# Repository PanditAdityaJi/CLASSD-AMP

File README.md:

# Class-D Audio Amplifier — NE555 PWM

A low-power Class-D audio amplifier built around the NE555 timer as a PWM generator. The design covers the full signal path from microphone/line input to an 8 Ω speaker, with LTspice simulation and a KiCad PCB layout included.

---

## How It Works

```
Audio In ──► opamp ──► NE555 ──► BJT Driver ──► PMOS/NMOS ──► LC Filter ──► Speaker
            Comparator   PWM      (Q1/Q2)        Half-Bridge    33µH/470nF
```

The audio signal and a triangle carrier are compared by an op-amp running open-loop. The comparator output triggers the NE555, which produces a PWM waveform whose duty cycle tracks the audio amplitude. A complementary BJT pair buffers the PWM to fast-charge the MOSFET gates of an (PMOS) /  (NMOS) half-bridge. An LC low-pass filter strips the switching harmonics, leaving a clean audio signal for the speaker.

## NE555 Pin Connections

| Pin | Name | Connection |
|-----|------|------------|
| 1 | GND  | Ground plane |
| 2 | TRIG | Triangle carrier via 1 nF AC-coupling cap (C2) |
| 3 | OUT  | PWM → gate driver through 100 Ω series resistor (R6) |
| 4 | RST  | Tied directly to VCC — **never** to OUT |
| 5 | CV   | 10 nF cap (C3) to GND — decouples internal divider |
| 6 | THRS | Timing capacitor + R3/R4 network |
| 7 | DIS  | Between R3 (1 kΩ) and R4 (3.3 kΩ) |
| 8 | VCC  | 12 V supply |

---

## Key Design Decisions

**Why NE555 instead of a microcontroller?** Frequency is set entirely by passive components — no firmware, no clock dependency.

**Why a BJT driver stage?** Power MOSFETs have several nF of gate capacitance. Driving them straight from the 555 output produces slow edges and shoot-through overlap. The emitter follower charges and discharges the gates in tens of nanoseconds.

**Why PMOS + NMOS instead of dual N-channel with a bootstrap?** Simpler gate drive — no floating supply needed for the high side. The pair has low enough R_DS(on) (0.5–1.5 Ω) that conduction loss is small against the 8 Ω load.

**Why 100 Ω on the gate (R6)?** Without it the gate trace resonates with the MOSFET input capacitance at hundreds of MHz. 100 Ω damps the ring without slowing the edge enough to increase switching loss.

**Why 33 µH / 0.47 µF for the LC filter?** The cut-off lands at roughly 300 kHz, giving >40 dB/decade roll-off. Film caps were specified over ceramics because ceramics of this value suffer severe DC-bias derating that would shift the pole under signal swing.

**Why matched R5 = R8 = 1 kΩ in the triangle generator?** Equal resistors make the rising and falling slopes identical, producing a symmetric carrier. An asymmetric carrier introduces even-order harmonics and a DC offset at the speaker.

---

## Bill of Materials

| Ref | Part | Value | Notes |
|-----|------|-------|-------|
| U1 | NE555D | — | SOIC-8 |
| U2 | LMV321 | — | SOT-23-5, open-loop comparator |
| Q1 | 2N3904 | — | NPN gate driver |
| Q2 | 2N3906 | — | PNP gate driver |
| Q3 | IRF9540 | — | PMOS high-side switch |
| Q4 | IRF540  | — | NMOS low-side switch |
| L1 | Inductor | 33 µH | Ferrite core, ≥ 3 A rated |
| R1 | Resistor | 100 kΩ | Input bias divider |
| R2 | Resistor | 100 kΩ | Input bias divider |
| R3 | Resistor | 1 kΩ   | 555 timing (charge) |
| R4 | Resistor | 3.3 kΩ | 555 timing (discharge) |
| R5 | Resistor | 1 kΩ   | Triangle generator |
| R6 | Resistor | 100 Ω  | Gate series damping |
| R7 | Resistor | 8 Ω    | Speaker load |
| R8 | Resistor | 1 kΩ   | Triangle generator |
| C1 | Capacitor | 10 nF  | Audio input AC-coupling |
| C2 | Capacitor | 1 nF   | TRIG AC-coupling |
| C3 | Capacitor | 10 nF  | CV pin bypass |
| C4 | Capacitor | 10 nF  | Triangle timing |
| C5 | Capacitor | 0.47 µF | LC filter (film) |
| C6 | Capacitor | 0.47 µF | Output filter / DC-block (film) |
| J2 | Connector | 2-pin | Power input (24 V) |
| J3 | Connector | 2-pin | Audio input |
| J4 | Connector | 2-pin | Speaker output |
| LS1 | Speaker | 8 Ω | — |

---

## Simulation

Simulated end-to-end in LTspice with a 1 kHz / 0.5 V sine test tone.

**Verified nodes:**

- **V(triangle)** — symmetric carrier, 3.4–3.6 V swing at the carrier frequency.
- **V(gate)** — clean PWM from the 555 output stage.
- **V(switching)** — half-bridge output, full rail-to-rail (0 V ↔ 24 V).
- **V(audio_out)** — filtered output; residual ripple is only a few millivolts.

**FFT results:**

- Audio_out shows the 1 kHz tone near −55 dB with harmonics below −140 dB across the audio band.
- Switching node shows the expected carrier and odd harmonics near 100 kHz.

---

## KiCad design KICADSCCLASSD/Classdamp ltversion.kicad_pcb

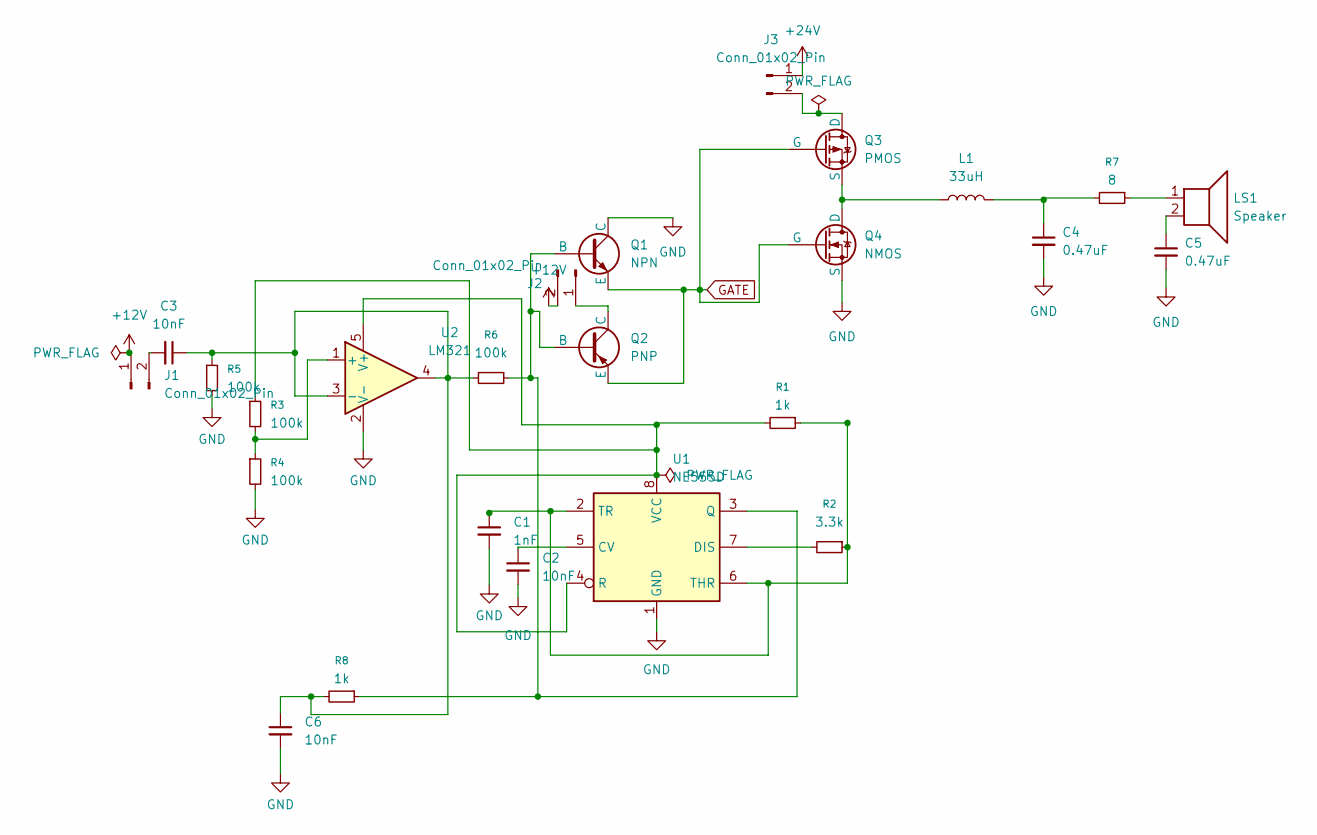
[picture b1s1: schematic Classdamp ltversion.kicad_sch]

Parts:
C1: 1nF; C_0201_0603Metric_Pad0.64x0.40mm_HandSolder
C2, C3, C6: 10nF; C_0402_1005Metric_Pad0.74x0.62mm_HandSolder
C4, C5: 0.47uF; C_0402_1005Metric_Pad0.74x0.62mm_HandSolder
J1, J2, J3: Conn_01x02_Pin; PhoenixContact_MCV_1,5_2-GF-5.08_1x02_P5.08mm_Vertical_Thre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
L1: 33uH; L_1206_3216Metric_Pad1.22x1.90mm_HandSolder
LS1: Speaker; MagneticBuzzer_ProSignal_ABT-410-RC
Q1: NPN; SOT-23
Q2: PNP; SOT-23
Q3: PMOS; TO-92
Q4: NMOS; TO-92
R1, R8: 1k; R_0201_0603Metric_Pad0.64x0.40mm_HandSolder
R2: 3.3k; R_0201_0603Metric_Pad0.64x0.40mm_HandSolder
R3, R4, R5, R6: 100k; R_0508_1220Metric_Pad1.12x2.15mm_HandSolder
R7: 8; R_0612_1632Metric_Pad1.18x3.40mm_HandSolder
U1: NE555D; SOIC-8_3.9x4.9mm_P1.27mm
U2: LM321; SOT-23-5

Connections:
+12V: J1.1, J2.2
+24V: J3.1
GATE: Q1.3 (E), Q2.3 (E), Q3.2 (G), Q4.2 (G)
GND: C1.2, C2.2, C4.2, C5.2, C6.2, Q1.1 (C), Q4.3 (S), R4.2, R5.2, U1.1 (GND), U2.2 (V-)
unnamed: C4.1, L1.2, R7.2
unnamed: C5.1, LS1.2
unnamed: C3.2, J1.2
unnamed: J2.1, Q2.1 (C)
unnamed: J3.2, Q3.1 (D)
unnamed: LS1.1, R7.1
unnamed: Q1.2 (B), Q2.2 (B), R6.1, R8.1, U1.3 (Q)
unnamed: L1.1, Q3.3 (S), Q4.1 (D)
unnamed: C2.1, U1.5 (CV)
unnamed: R2.2, U1.7 (DIS)
unnamed: R1.2, R3.1, U1.4 (R), U1.8 (VCC), U2.5 (V+)
unnamed: C1.1, R1.1, R2.1, U1.2 (TR), U1.6 (THR)
unnamed: R3.2, R4.1, U2.1 (+)
unnamed: C3.1, C6.1, R5.1, R6.2, R8.2, U2.3 (-), U2.4

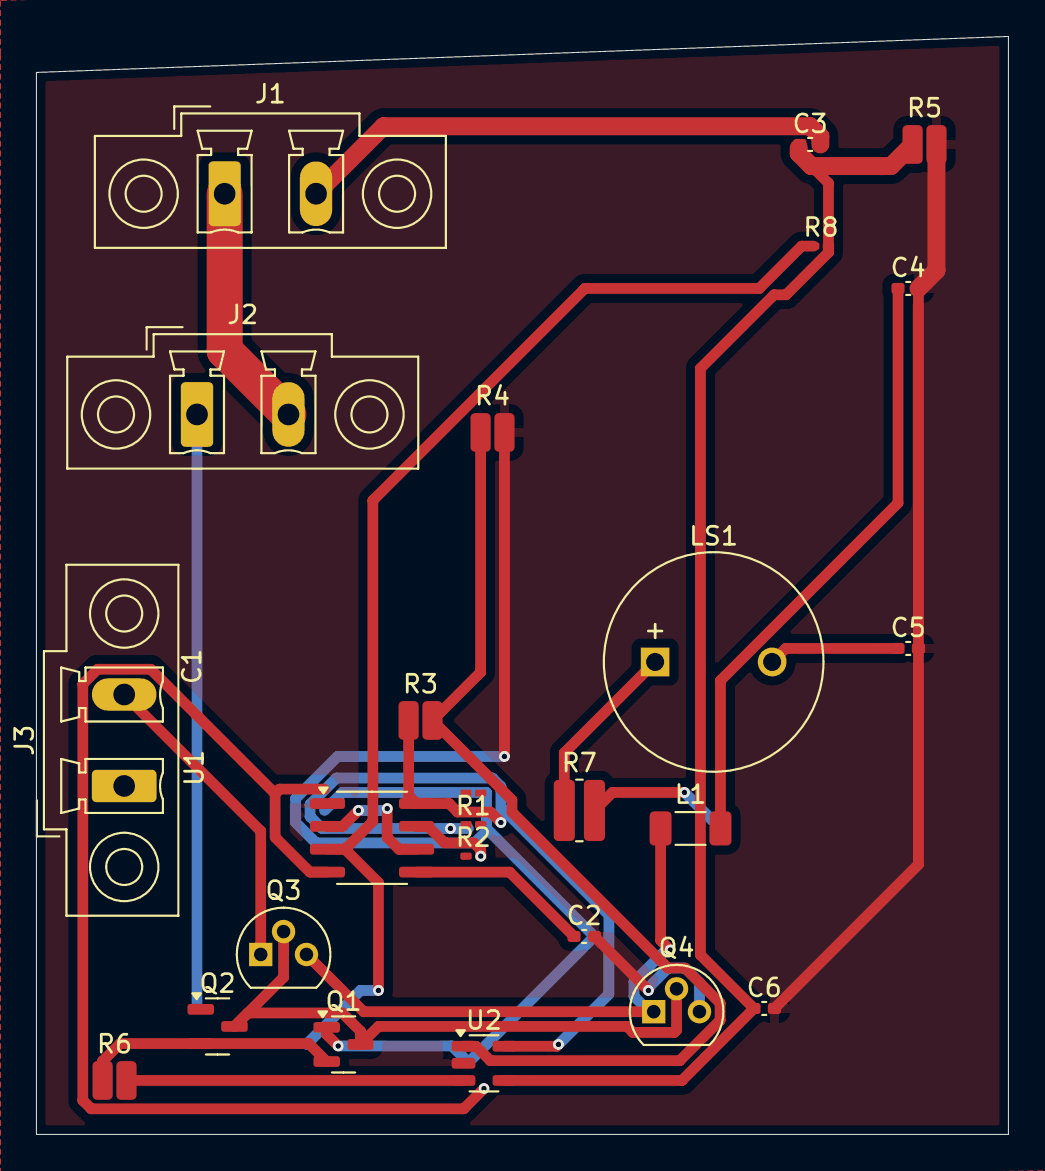
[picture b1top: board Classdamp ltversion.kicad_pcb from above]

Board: 2 copper layers, 54.0 x 61.0 mm, 25 parts (0 on the bottom side), 17 nets.

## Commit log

2026-02-01 Create csr
2026-02-01 Create csr1
2026-02-01 Create CS
